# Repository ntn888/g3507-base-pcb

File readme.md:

## mspm0g3507 minimal dev board

### Parts list

Red LED 0805- C965812

Blue LED 0805- C965817

Resistor 1K 0805 x2- C95781

Resistor 47K 0805- C126351

Resistor 330 0805- C105877

Resistor 100K 0.1% 0805- C122537

Cap 10nF 0805- C1710

Cap 10uF 0805- C15850

Cap 0.1uF 0805- C49678

Cap 0.47uF 0805- C106843

---

sw_push- C720477

conn01x04 C42431821

conn01x15 C2337

uC- C22362630

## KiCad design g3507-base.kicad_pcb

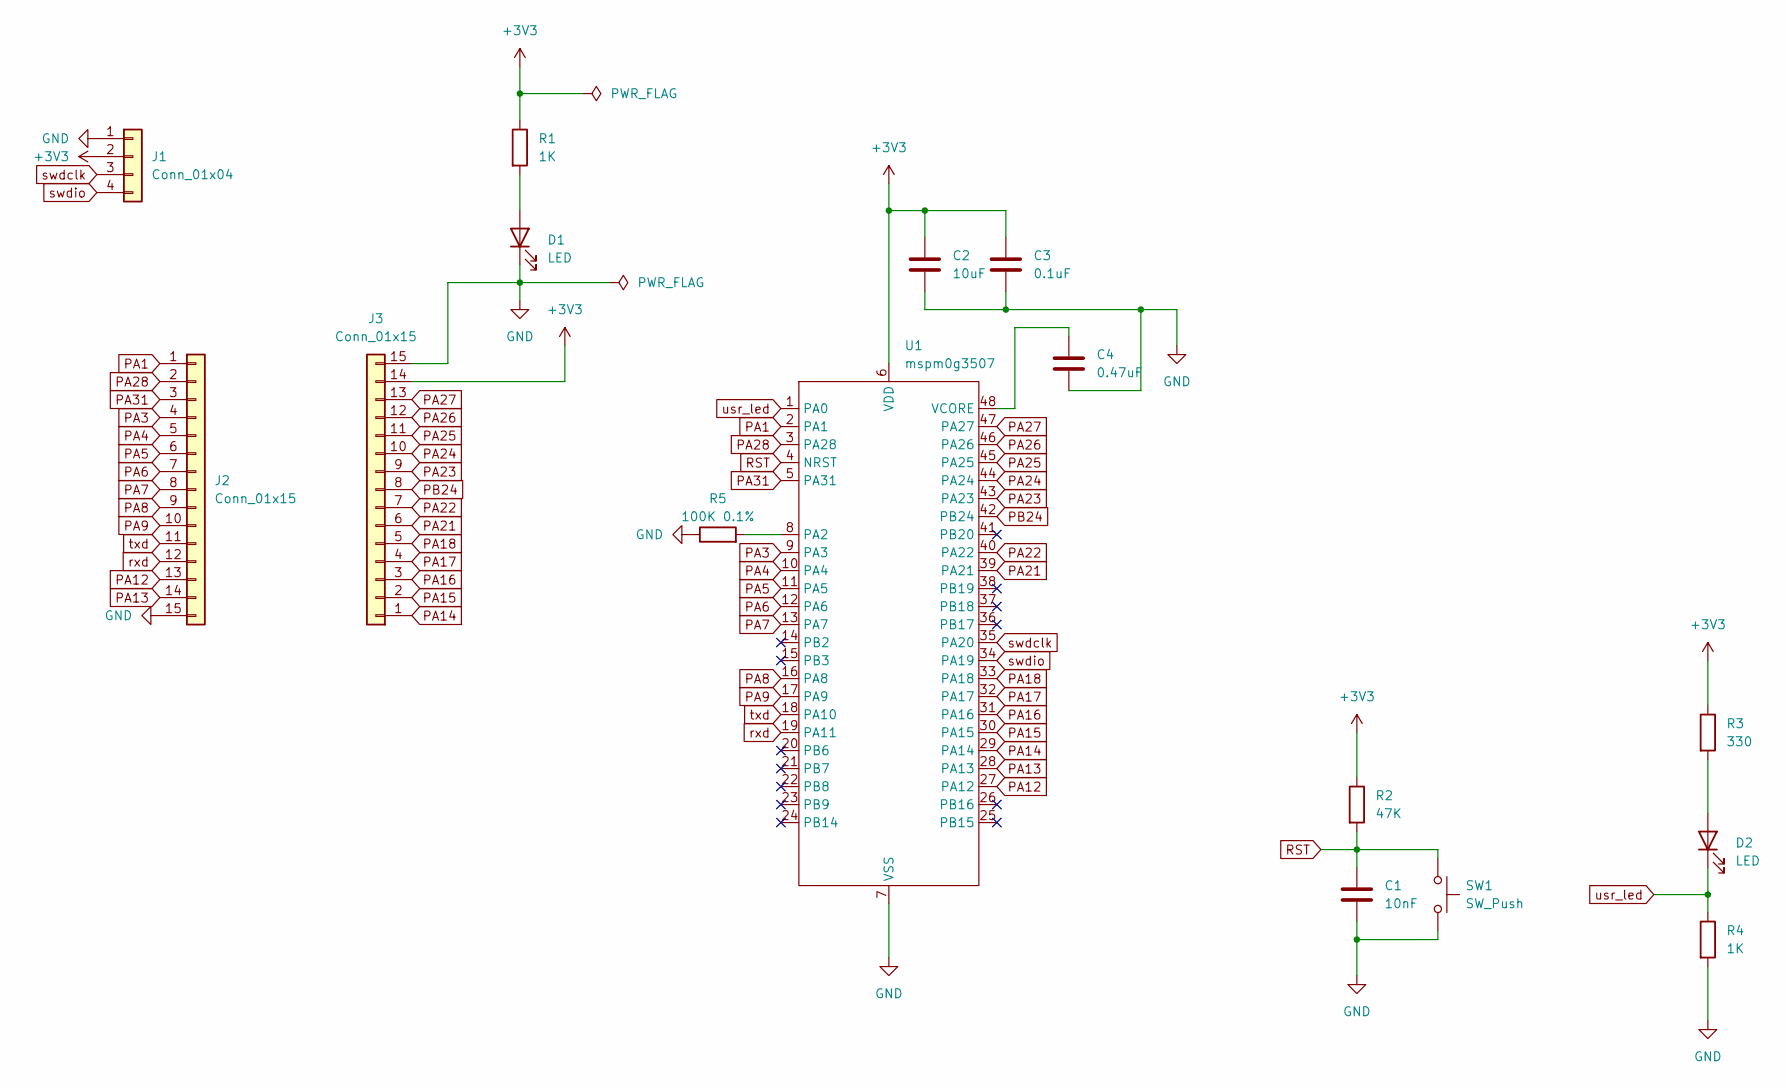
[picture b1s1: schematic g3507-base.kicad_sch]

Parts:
C1: 10nF; C_0805_2012Metric_Pad1.18x1.45mm_HandSolder
C2: 10uF; C_0805_2012Metric_Pad1.18x1.45mm_HandSolder
C3: 0.1uF; C_0805_2012Metric_Pad1.18x1.45mm_HandSolder
C4: 0.47uF; C_0805_2012Metric_Pad1.18x1.45mm_HandSolder
D1, D2: LED; LED_0805_2012Metric_Pad1.15x1.40mm_HandSolder
J1: Conn_01x04; PinHeader_1x04_P2.54mm_Horizontal
J2, J3: Conn_01x15; PinHeader_1x15_P2.54mm_Vertical
R1, R4: 1K; R_0805_2012Metric_Pad1.20x1.40mm_HandSolder
R2: 47K; R_0805_2012Metric_Pad1.20x1.40mm_HandSolder
R3: 330; R_0805_2012Metric_Pad1.20x1.40mm_HandSolder
R5: 100K 0.1%; R_0805_2012Metric_Pad1.20x1.40mm_HandSolder
SW1: SW_Push; SW_SPST_TS-1088-AR02016
U1: mspm0g3507; LQFP-48_7x7mm_P0.5mm

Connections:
+3V3: C2.1, C3.1, J1.2, J3.14, R1.1, R2.1, R3.1, U1.6 (VDD)
GND: C1.2, C2.2, C3.2, C4.2, D1.1 (K), J1.1, J2.15, J3.15, R4.2, R5.1, SW1.2, U1.7 (VSS)
unnamed: D1.2 (A), R1.2
unnamed: D2.2 (A), R3.2
unnamed: R5.2, U1.8 (PA2)
unnamed: C4.1, U1.48 (VCORE)
PA1: J2.1, U1.2 (PA1)
PA3: J2.4, U1.9 (PA3)
PA4: J2.5, U1.10 (PA4)
PA5: J2.6, U1.11 (PA5)
PA6: J2.7, U1.12 (PA6)
PA7: J2.8, U1.13 (PA7)
PA8: J2.9, U1.16 (PA8)
PA9: J2.10, U1.17 (PA9)
PA12: J2.13, U1.27 (PA12)
PA13: J2.14, U1.28 (PA13)
PA14: J3.1, U1.29 (PA14)
PA15: J3.2, U1.30 (PA15)
PA16: J3.3, U1.31 (PA16)
PA17: J3.4, U1.32 (PA17)
PA18: J3.5, U1.33 (PA18)
PA21: J3.6, U1.39 (PA21)
PA22: J3.7, U1.40 (PA22)
PA23: J3.9, U1.43 (PA23)
PA24: J3.10, U1.44 (PA24)
PA25: J3.11, U1.45 (PA25)
PA26: J3.12, U1.46 (PA26)
PA27: J3.13, U1.47 (PA27)
PA28: J2.2, U1.3 (PA28)
PA31: J2.3, U1.5 (PA31)
PB24: J3.8, U1.42 (PB24)
RST: C1.1, R2.2, SW1.1, U1.4 (NRST)
rxd: J2.12, U1.19 (PA11)
swdclk: J1.3, U1.35 (PA20)
swdio: J1.4, U1.34 (PA19)
txd: J2.11, U1.18 (PA10)
usr_led: D2.1 (K), R4.1, U1.1 (PA0)

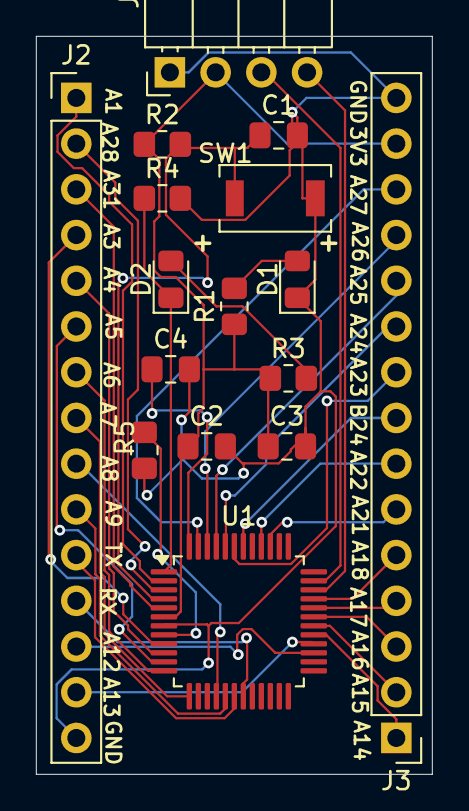
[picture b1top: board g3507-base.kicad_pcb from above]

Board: 2 copper layers, 22.0 x 41.0 mm, 16 parts (0 on the bottom side), 37 nets.

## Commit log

2026-02-04 fix readme newlines
